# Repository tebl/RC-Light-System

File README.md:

# RC Light System
The *Arduino Starter Kit*, the official one with a bunch of parts and a book, was my first real introduction to working with electronics. Sure, I had put a new power plug on various things as a child of a different time that this one. What I hadn't done, was learn how to not blow things up when trying out new things. Arduino is pretty much perfect for that. Not in that you won't blow things up, it's more a case of blowing up really cheap parts and you rarely, if ever, actually set anything on fire. Working through it all, I wanted to create a project of my own - I would make a better light system for RCs.

Yeah! Turns out that doing exactly that, requires understanding a lot more than simply plugging an LED into a breadboard and turning it on or off - there's logic levels, reading a PWM signal and then figuring out how to design your own PCBs. So I eventually put my parts in the infamous *"someday"* pile. A decade later, I've learned a few things and it was time to take something off that pile and try again! 

As I had a lot of fun doing it, I wanted to build a multitude of slightly different things around the same core theme - RCs, lighting and cool effects. For that reason I found it easier to organize them into their own sub-projects, so follow the links to the ones you are specifically interested in.

- [1> Projects](#1-projects)
  - [1.1> RC Light System](#11-rc-light-system)
  - [1.2> RC Exhaust](#12-rc-exhaust)
  - [1.3> RC Dashboard](#13-rc-dashboard)

# 1> Projects
For the technical details as well as information regarding the projects included in this specific github repository, consult the table below and follow along for the things that may interest you.  As each project will realistically end up being done in several different ways, they will each come with their own set of documentation as well as BOM-listings - these are organized by putting all that into the documentation for each module below it. Organized separately, you are also recommended to check out the [schematics](https://github.com/tebl/RC-Light-System/tree/main/documentation/schematic) for detailed information about how the electrical side of things work.

| Module                            | Description                                      |
| --------------------------------- | ------------------------------------------------ | 
| [RC Light System](#11-rc-light-system)  | A functional light system for RCs. It's big, bulky and does mostly what I want it to do.
| [RC Exhaust](#12-rc-exhaust) | Controls an RGB LED mounted inside the exhaust pipe of an RC. On heavy throttle it starts glowing red, ease up on the trottle afterwards and you get flashing colours as it backfires.
| [RC Dashboard](#13-rc-dashboard) | Connected to the receiver, it shows a digital throttle gauge on a small OLED-screen.

## 1.1> RC Light System
This is the project I had originally intended to design, almost a decade earlier. A lighting system with some kind of recognizable intelligence to it. More specifically, something that wouldn't turn on the blinkers when turning the wheel. I could always just cut the wire, but I wanted it to work so that it felt more *scale* - turning on the blinker when cornering around a racetrack at subsonic speeds wasn't it. My second requirement was that it should be detachable by cable, mostly so that the electronics mounted on the chassis could be separated from those that are stuck to the body.

I can't physically work with small components, so as for any practical usage you will need a lot of space to install this - possibly a truck of some kind. Other than that, consider it *educational* material for anyone that wants to connect an Arduino to an RC-receiver.

| Module                            | Description                                      |
| --------------------------------- | ------------------------------------------------ | 
| [RC Light System](https://github.com/tebl/RC-Light-System/tree/main/RC%20Light%20System)  | Main module for mounting on chassis, uses Arduino Pro Micro.
| [RC Light System Output](https://github.com/tebl/RC-Light-System/tree/main/RC%20Light%20System%20Output)  | Output-module for mounting on a body. Four sets of two LEDs can be combined to have two levels of brightness.
| [RC Light System Output Mini](https://github.com/tebl/RC-Light-System/tree/main/RC%20Light%20System%20Output%20Mini)  | Output-module for mounting on a body. Slightly smaller than the other one, with almost none of the interesting features apart from turning LEDs on and off.

## 1.2> RC Exhaust
Working with the [RC Light System](#11-rc-light-system), I came across small metal exhaust pipes for 1:10 RCs on AliExpress. Arriving in the mail a couple of months later I knew I had to install them in something, given that they were designed to fit an LED inside it - I wanted something more exciting than a basic effect. I wanted it to glow red on heavy throttle, backfire when easing up on the throttle and so on!

| Module                            | Description                                      |
| --------------------------------- | ------------------------------------------------ | 
| [RC Exhaust Digispark](https://github.com/tebl/RC-Light-System/tree/main/RC%20Exhaust%20Digispark)  | Exhaust-module based around Digispark, with capability for RGB colour LED.

## 1.3> RC Dashboard
Tightly related to the [RC Exhaust](#12-rc-exhaust) in terms of implementation, mostly because I initially couldn't get it to work - so in the end I had to put a screen on one, all in order to figure out all the ways it had initially failed to work. That doesn't sound like a fun thing to build, but when doing it I had an idea - why not mount the screen inside the interior of an RC car? Cars generally have those, we call them *"dashboards"*.

An electric RC doesn't exactly have a lot of telemetry that's available to plug into, but at least I can put a throttle gauge on it. Nowadays you'd probably want an analog one, but I designed this one to mimic the digital future that was on display in a limited selection of 80s and 90s cars - check out [The definitive collection of cool 1980s digital dashboards in Euro cars
](https://drivemag.com/red-calipers/the-definitive-collection-of-cool-1980s-digital-dashboards-in-euro-cars/) to see some examples of what I'm talking about here.

| Module                            | Description                                      |
| --------------------------------- | ------------------------------------------------ | 
| [RC Dashboard Digispark](https://github.com/tebl/RC-Light-System/tree/main/RC%20Dashboard%20Digispark)  | Dashboard-module based around Digispark.

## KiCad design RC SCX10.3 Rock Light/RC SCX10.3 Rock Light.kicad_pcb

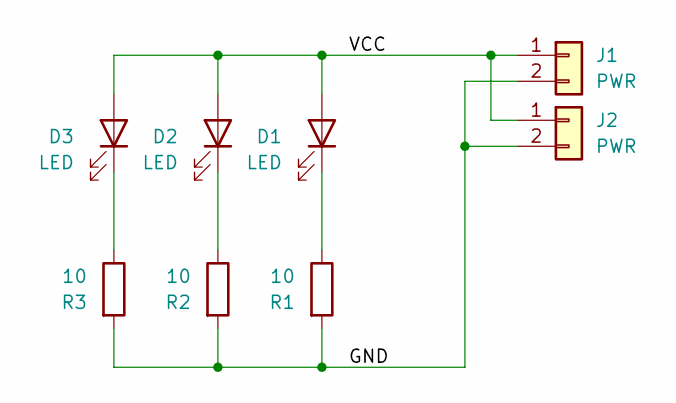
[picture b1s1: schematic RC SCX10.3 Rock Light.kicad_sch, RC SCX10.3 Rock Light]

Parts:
D1, D2, D3: LED; LED_1206_3216Metric_Pad1.42x1.75mm_HandSolder
J1, J2: PWR; edge_pins_1x02
R1, R2, R3: 10; R_1206_3216Metric_Pad1.30x1.75mm_HandSolder

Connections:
/GND: J1.2, J2.2, R1.2, R2.2, R3.2
/VCC: D1.2 (A), D2.2 (A), D3.2 (A), J1.1, J2.1
unnamed: D1.1 (K), R1.1
unnamed: D2.1 (K), R2.1
unnamed: D3.1 (K), R3.1

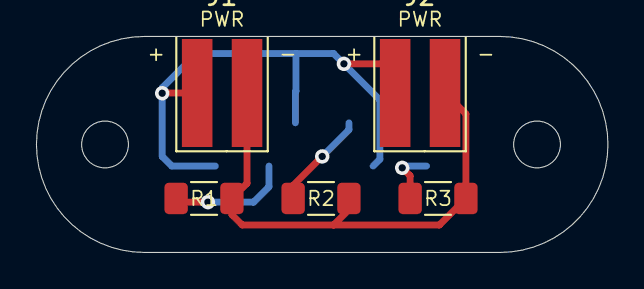
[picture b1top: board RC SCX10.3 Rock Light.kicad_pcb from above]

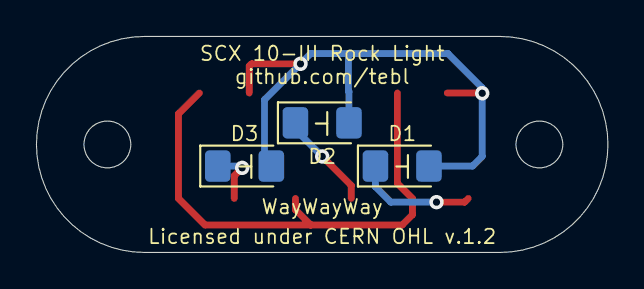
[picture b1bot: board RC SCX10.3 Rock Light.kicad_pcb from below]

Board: 2 copper layers, 31.8 x 12.0 mm, 8 parts (3 on the bottom side), 5 nets.

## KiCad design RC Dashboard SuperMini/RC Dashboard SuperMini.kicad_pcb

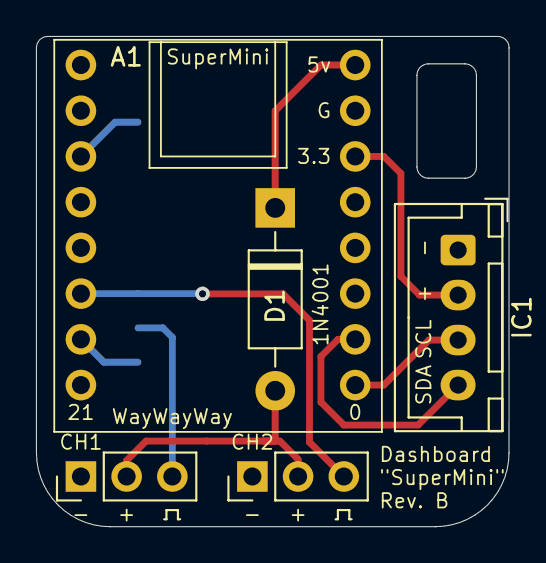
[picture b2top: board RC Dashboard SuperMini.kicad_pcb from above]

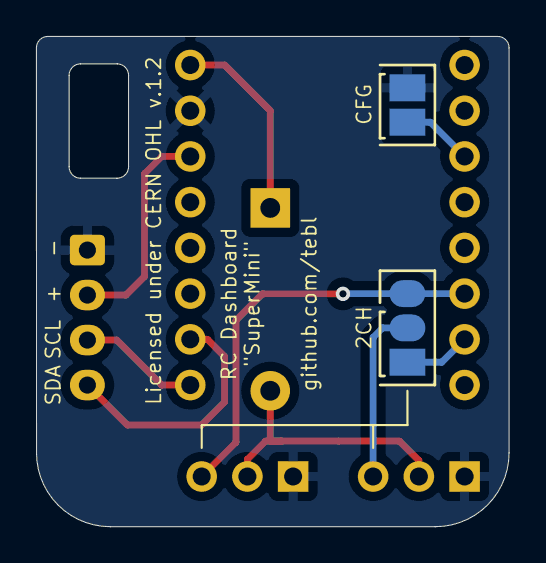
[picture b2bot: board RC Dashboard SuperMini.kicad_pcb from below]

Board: 2 copper layers, 26.3 x 27.2 mm, 7 parts (2 on the bottom side), 10 nets.

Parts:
A1: SuperMini; SuperMini_ESP32_C3
D1: 1N4001; D_DO-41_SOD81_P10.16mm_Horizontal
IC1: 0.91_I2C_OLED; JST_XH_B4B-XH-A_1x04_P2.50mm_Vertical
J5: CH1; PinHeader_1x03_P2.54mm_Vertical
J6: CH2; PinHeader_1x03_P2.54mm_Vertical
JP1: 2CH; select2
JP3: CFG; bridge

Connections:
+3V3: A1.14 (3V3), IC1.2 (VCC)
/6v: D1.2 (A), J5.2 (BEC), J6.2 (BEC)
/CFG_2: A1.3 (GPIO7), JP3.2 (B)
/SCL: A1.9 (GPIO0), IC1.3 (SCL)
/SDA: A1.10 (GPIO1), IC1.4 (SDA)
CH1: A1.7 (GPIO20), JP1.1 (A)
CH2: A1.6 (GPIO10), J6.3 (VCC), JP1.3 (B)
GND: A1.15 (GND), IC1.1 (GND), J5.1 (GND), J6.1 (GND), JP3.1 (A)
unnamed: J5.3 (VCC), JP1.2 (C)
VBUS: A1.16 (5v), D1.1 (K)

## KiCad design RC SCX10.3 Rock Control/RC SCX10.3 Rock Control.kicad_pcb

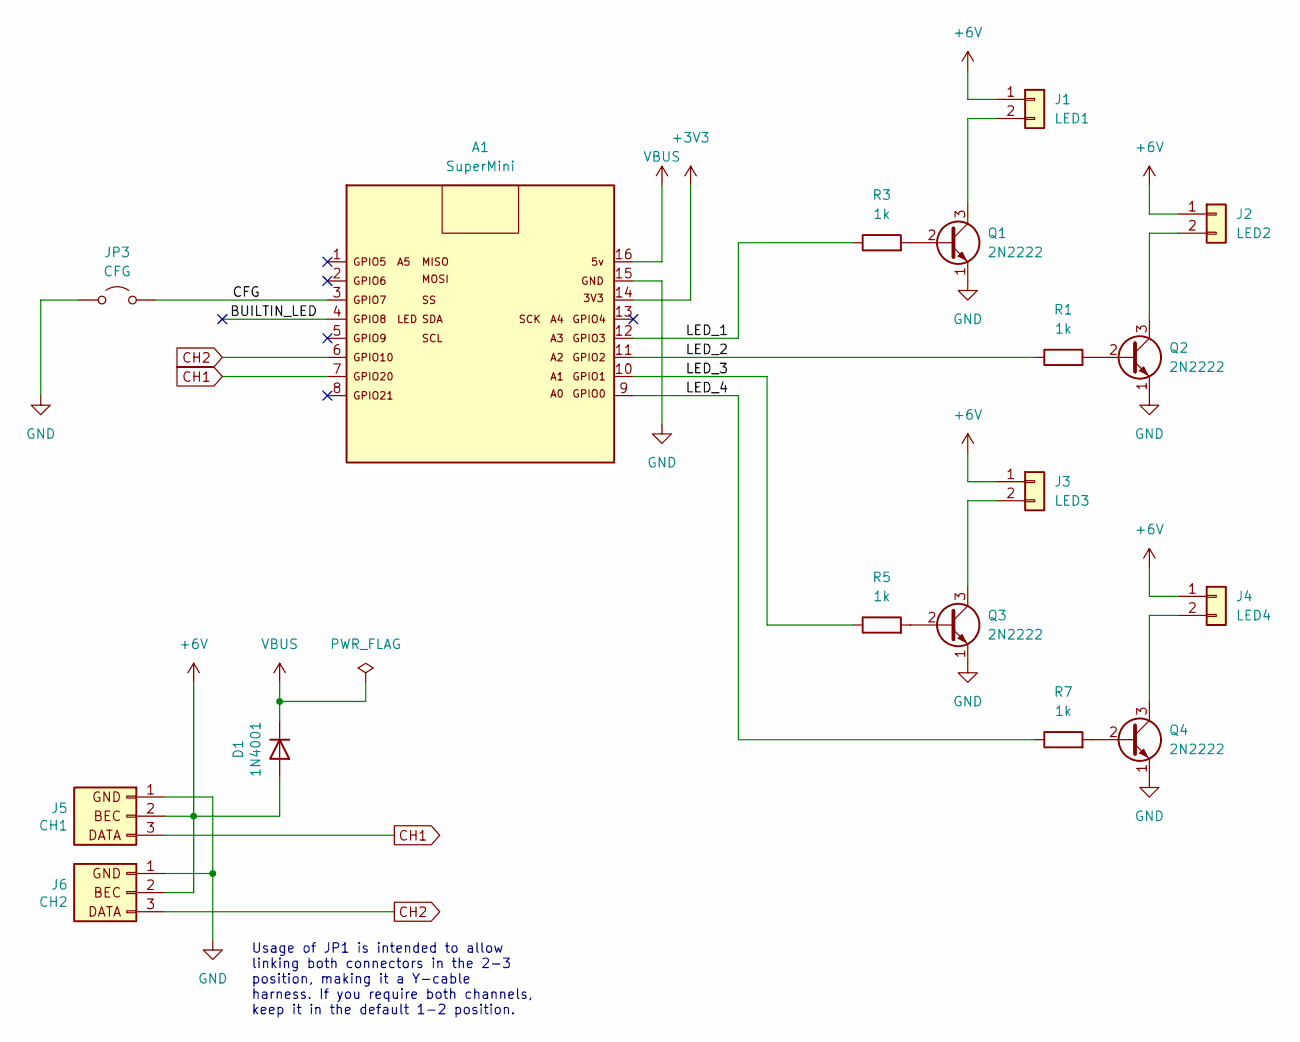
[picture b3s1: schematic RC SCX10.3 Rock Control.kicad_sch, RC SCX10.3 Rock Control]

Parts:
A1: SuperMini; SuperMini_ESP32_C3
D1: 1N4001; D_DO-41_SOD81_P10.16mm_Horizontal
J1: LED1; JST_XH_B2B-XH-A_1x02_P2.50mm_Vertical
J2: LED2; JST_XH_B2B-XH-A_1x02_P2.50mm_Vertical
J3: LED3; JST_XH_B2B-XH-A_1x02_P2.50mm_Vertical
J4: LED4; JST_XH_B2B-XH-A_1x02_P2.50mm_Vertical
J5: CH1; PinHeader_1x03_P2.54mm_Vertical
J6: CH2; PinHeader_1x03_P2.54mm_Vertical
JP3: CFG; bridge
Q1, Q2, Q3, Q4: 2N2222; TO-92_Inline_Wide
R1, R3, R5, R7: 1k; R_Axial_DIN0207_L6.3mm_D2.5mm_P7.62mm_Horizontal

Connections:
+3V3: A1.14 (3V3)
+6V: D1.2 (A), J1.1, J2.1, J3.1, J4.1, J5.2 (BEC), J6.2 (BEC)
/BUILTIN_LED: A1.4 (GPIO8)
/CFG: A1.3 (GPIO7), JP3.2 (B)
/LED_1: A1.12 (GPIO3), R3.1
/LED_2: A1.11 (GPIO2), R1.1
/LED_3: A1.10 (GPIO1), R5.1
/LED_4: A1.9 (GPIO0), R7.1
CH1: A1.7 (GPIO20), J5.3 (VCC)
CH2: A1.6 (GPIO10), J6.3 (VCC)
GND: A1.15 (GND), J5.1 (GND), J6.1 (GND), JP3.1 (A), Q1.1 (E), Q2.1 (E), Q3.1 (E), Q4.1 (E)
unnamed: J1.2, Q1.3 (C)
unnamed: J2.2, Q2.3 (C)
unnamed: J3.2, Q3.3 (C)
unnamed: J4.2, Q4.3 (C)
unnamed: Q1.2 (B), R3.2
unnamed: Q2.2 (B), R1.2
unnamed: Q3.2 (B), R5.2
unnamed: Q4.2 (B), R7.2
VBUS: A1.16 (5v), D1.1 (K)

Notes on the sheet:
Usage of JP1 is intended to allow linking both connectors in the 2-3 position, making it a Y-cable harness. If you require both channels, keep it in the default 1-2 position.

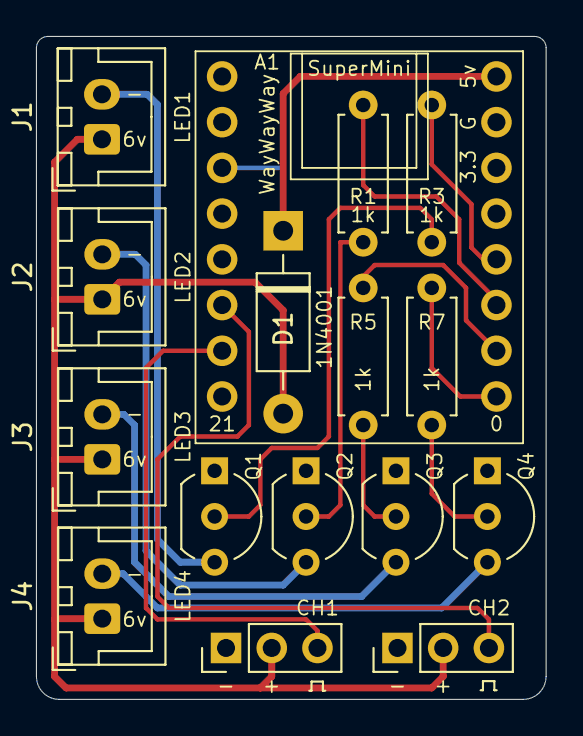
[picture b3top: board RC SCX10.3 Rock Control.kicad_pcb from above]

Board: 2 copper layers, 28.3 x 36.8 mm, 17 parts (1 on the bottom side), 18 nets.

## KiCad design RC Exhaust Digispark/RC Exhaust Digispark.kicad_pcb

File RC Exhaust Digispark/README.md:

# RC Exhaust (Digispark)
Working with the RC Light System, I came across a small metal exhaust pipe for 1:10 RCs on AliExpress. Arriving in the mail a couple of months later, I knew I had to install them in something. Careful measuring revealed that they were designed to fit an LED inside it, and later versions that I picked up even came with one included. I did however want something that was a little more dynamic than a static LED could provide and while I could have gone with the 555, I went the full route of the Attiny85. Granted, I did have some Digispark modules that I'd never found a use for. Until now.

The plan was to have the exhaust pipe glow red on heavy throttle, then backfire when easing up on the throttle. It'll throw in some regular sparks here and there to make it come alive a bit more than that, but the code is included here if you want something else.

- [1> Building the device](#1-building-the-device)
- [2> Schematic](#2-schematic)
- [3> BOM](#3-bom)

# 1> Building the device
Building the device should be a straight-forward affair, you just solder the meager selection of components into place. Pay attention to keep the alignment of the parts somewhat straight, then you should be good. This documentation was written with a board that looks like the following in mind, but note that the github-repository may contain changes that have yet to be tested (therefore, it is recommend that PCBs are ordered using PCBWay links listed in the BOM).

The Attiny85 is a 5v chip, and we're connecting it to a 6v source due to it living inside an RC. Normally that would toast it as we're working outside the acceptable ranges, but we're using a diode with a voltage drop that's up to 0.7v - bringing us withing the tolerances of the chip. As for installation, just match the silver stripe on the component to the stripe part on the board and you're good to go.

Resistors should be added, but you can *probably* skip R4 and R5 - those form a voltage divider in case the receiver is sending out a signal that's above 3.3v. I've not encountered any of those, but then again - I don't have RC equipment older than a decade or so. Link the corresponding *NO_VOL_DIV* pads on the back of it if you've skipped them.

The three at the bottom are for the LEDs, here you may need to match the datasheet for your specific LED, per colour, in order to arrive at a suitable resistor value. Consult a [LED Series Resistor Calculator](https://www.digikey.com/en/resources/conversion-calculators/conversion-calculator-led-series-resistor) if you need to (set supply voltage to 5.3v, fill in 10mA current for blue/green and 15mA for red).

The Digispark itself is then soldered on top, with straight pin headers between the two. It doesn't matter if you used the Digispark shaped like a "USB-key", or if it has a Micro-USB socket on it - they fit just the same. Personally I prefer the former as it is easier to wipe off compared to pulling debris out of a socket.

The LED must be attached to the board using a removable lead, which is why I'm using JST XH plugs on mine. When wiring for an RGB LED it must be a common anode variety, but you can use a normal LED as well - just wire it up to the board as *RED*. If you don't care about being able to reprogram the board later, you can just solder the wires directly. When soldering onto the LED legs, I recommend using heat shrink tubing to avoid any accidents. An easier alternative is to use a pre-wired red LED and just connect up those two leads, but won't look as fancy.

The left hand side is where you connect up the wire coming from the ESC, there are two here - mainly so that you could use it as a Y-lead without requiring any additional cables. Solder wires, or install pin headers depending on what you prefer.

# 2> Schematic
The supplied KiCad files should be sufficient as both a schematic and as a  starting point for ordering PCBs (basically you could just zip the contents of the export folder and upload that on a fabrication site), the schematic is also available in [PDF-format](https://github.com/tebl/RC-Light-System/tree/main/documentation/schematic) and this is what you'll need to print and work your way through when things fail to work as expected.

# 3> BOM
Most parts should be easy to get a hold of from your favourite local electronic component shop, but given that I don't have access to such shops where I live so everything was based on whatever I could get cheapest from eBay/AliExpress (free shipping, but plan on waiting 3-4 weeks for delivery). As I expect that most will build this adapter solely for MIDI-output, the values required for the MIDI input have been listed in parenthesis.

| Reference      | Item                                                  | Count | Order  |
| ---------------| ----------------------------------------------------- | ----- | ------ |
| Faceplate PCB  | Fabricate using Gerber files                          |     1 | PCBWay
| A1             | Digispark-module (with pin-headers)                   |     1 |
| D1 *           | 4-pin JST-XH socket                                   |     1 |
|                | 5mm LED, common-anode variety to 4-pin JST-XH plug    |     1 |
| D2             | 1N4001 diode (DO-41)                                  |     1 |
| J5,J6          | Straight pin-headers, alternatively wire a Y-splitter |     1 |
| R1             | 200 ohm resistor                                      |     1 |
| R2,R3          | 270 ohm resistor                                      |     2 |
| R4             | 10k ohm resistor                                      |    (1)|
| R5             | 20k ohm resistor                                      |    (1)|

*) You can come up with something else here, but JST-XH is what I recommend. They're keyed and locking so they won't come off very easily. For the LED, I recommend buying pre-wired 4-pin JST-XH leads with plugs already on it - you'll need to solder it to the individual LED legs though (use heat shrink tubing).

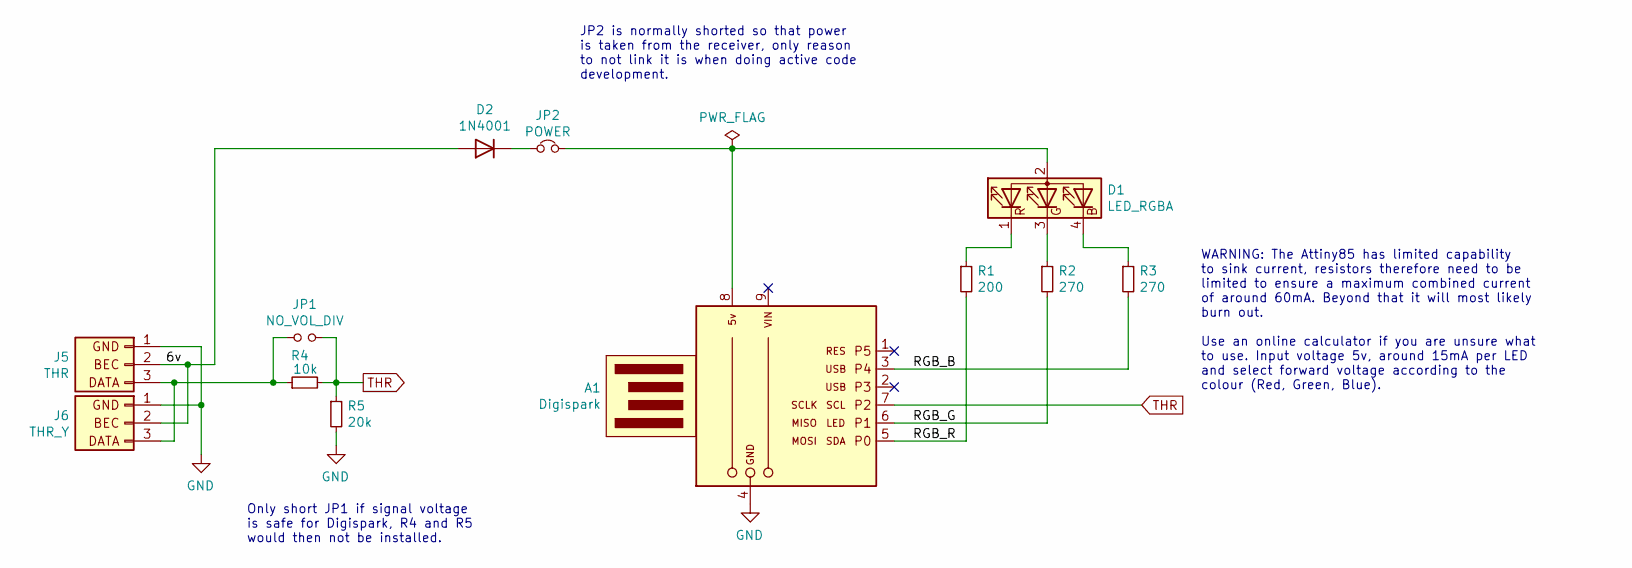
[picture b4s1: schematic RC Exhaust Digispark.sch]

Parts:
A1: Digispark
D1: LED_RGBA; JST_XH_B4B-XH-A_1x04_P2.50mm_Vertical
D2: 1N4001; D_DO-41_SOD81_P10.16mm_Horizontal
J5: THR; PinHeader_1x03_P2.54mm_Vertical
J6: THR_Y; PinHeader_1x03_P2.54mm_Vertical
JP1: NO_VOL_DIV; bridge_open
JP2: POWER; bridge
R1: 200; R_Axial_DIN0207_L6.3mm_D2.5mm_P7.62mm_Horizontal
R2, R3: 270; R_Axial_DIN0207_L6.3mm_D2.5mm_P7.62mm_Horizontal
R4: 10k; R_Axial_DIN0207_L6.3mm_D2.5mm_P7.62mm_Horizontal
R5: 20k; R_Axial_DIN0207_L6.3mm_D2.5mm_P7.62mm_Horizontal

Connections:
/6v: D2.2 (A), J5.2 (BEC), J6.2 (BEC)
/RGB_B: A1.3 (P4), R3.2
/RGB_G: A1.6 (P1), R2.2
/RGB_R: A1.5 (P0), R1.2
GND: A1.4 (GND), J5.1 (GND), J6.1 (GND), R5.2
unnamed: A1.8 (5v), D1.2 (A), JP2.2
unnamed: D1.1 (RK), R1.1
unnamed: D1.3 (GK), R2.1
unnamed: D1.4 (BK), R3.1
unnamed: D2.1 (K), JP2.1
unnamed: J5.3 (VCC), J6.3 (VCC), JP1.1, R4.1
THR: A1.7 (P2), JP1.2, R4.2, R5.1

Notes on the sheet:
Only short JP1 if signal voltage is safe for Digispark, R4 and R5 would then not be installed.
JP2 is normally shorted so that power is taken from the receiver, only reason to not link it is when doing active code development.
WARNING: The Attiny85 has limited capability to sink current, resistors therefore need to be limited to ensure a maximum combined current of around 60mA. Beyond that it will most likely burn out. Use an online calculator if you are unsure what to use. Input voltage 5v, around 15mA per LED and selec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

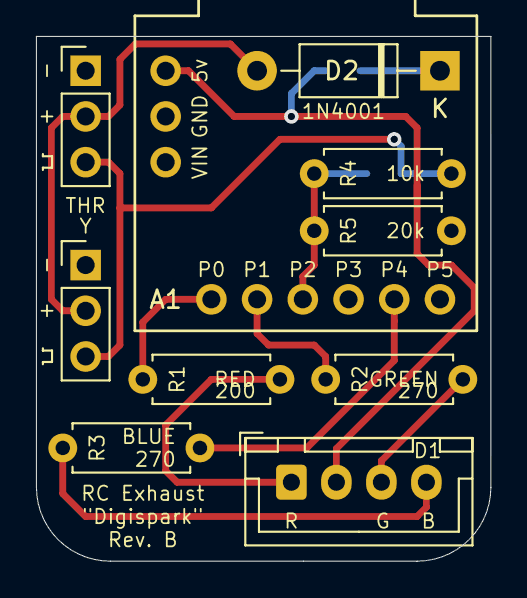
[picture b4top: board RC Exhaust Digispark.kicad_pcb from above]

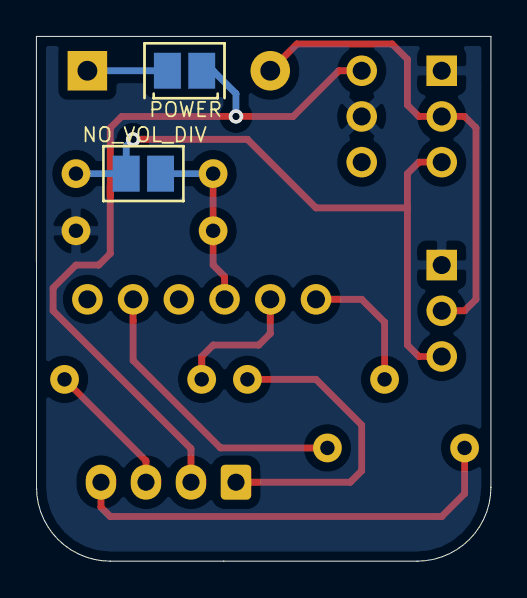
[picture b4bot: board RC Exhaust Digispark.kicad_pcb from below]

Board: 2 copper layers, 25.2 x 29.2 mm, 12 parts (2 on the bottom side), 12 nets.

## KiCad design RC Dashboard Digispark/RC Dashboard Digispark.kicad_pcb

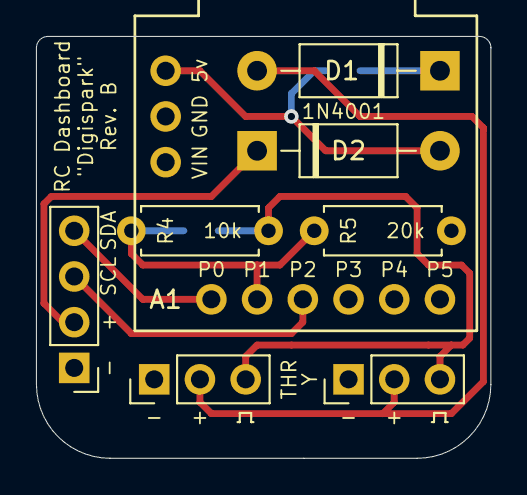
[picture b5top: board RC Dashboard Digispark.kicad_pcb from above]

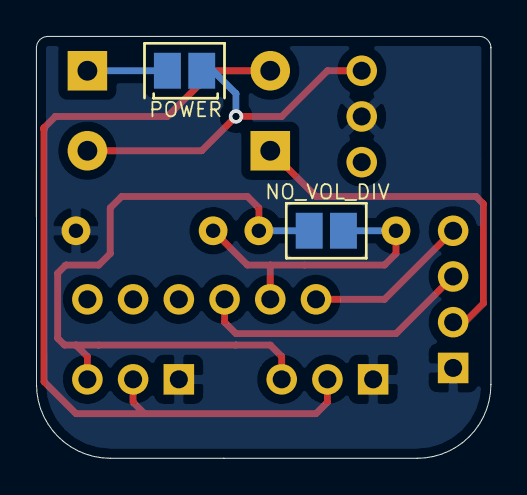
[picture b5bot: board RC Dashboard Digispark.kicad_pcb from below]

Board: 2 copper layers, 25.2 x 23.4 mm, 10 parts (2 on the bottom side), 9 nets.

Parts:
A1: Digispark
D1, D2: 1N4001; D_DO-41_SOD81_P10.16mm_Horizontal
IC1: 0.91_I2C_OLED; PinHeader_1x04_P2.54mm_Vertical
J5: THR; PinHeader_1x03_P2.54mm_Vertical
J6: THR_Y; PinHeader_1x03_P2.54mm_Vertical
JP1: NO_VOL_DIV; bridge_open
JP2: POWER; bridge
R4: 10k; R_Axial_DIN0207_L6.3mm_D2.5mm_P7.62mm_Horizontal
R5: 20k; R_Axial_DIN0207_L6.3mm_D2.5mm_P7.62mm_Horizontal

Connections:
/6v: D1.2, J5.2, J6.2
GND: A1.4, IC1.1, J5.1, J6.1, R5.2
unnamed: A1.5, IC1.4
unnamed: A1.7, IC1.3
unnamed: A1.8, D2.2, JP2.2
unnamed: D1.1, JP2.1
unnamed: D2.1, IC1.2
unnamed: J5.3, J6.3, JP1.1, R4.1
THR: A1.6, JP1.2, R4.2, R5.1

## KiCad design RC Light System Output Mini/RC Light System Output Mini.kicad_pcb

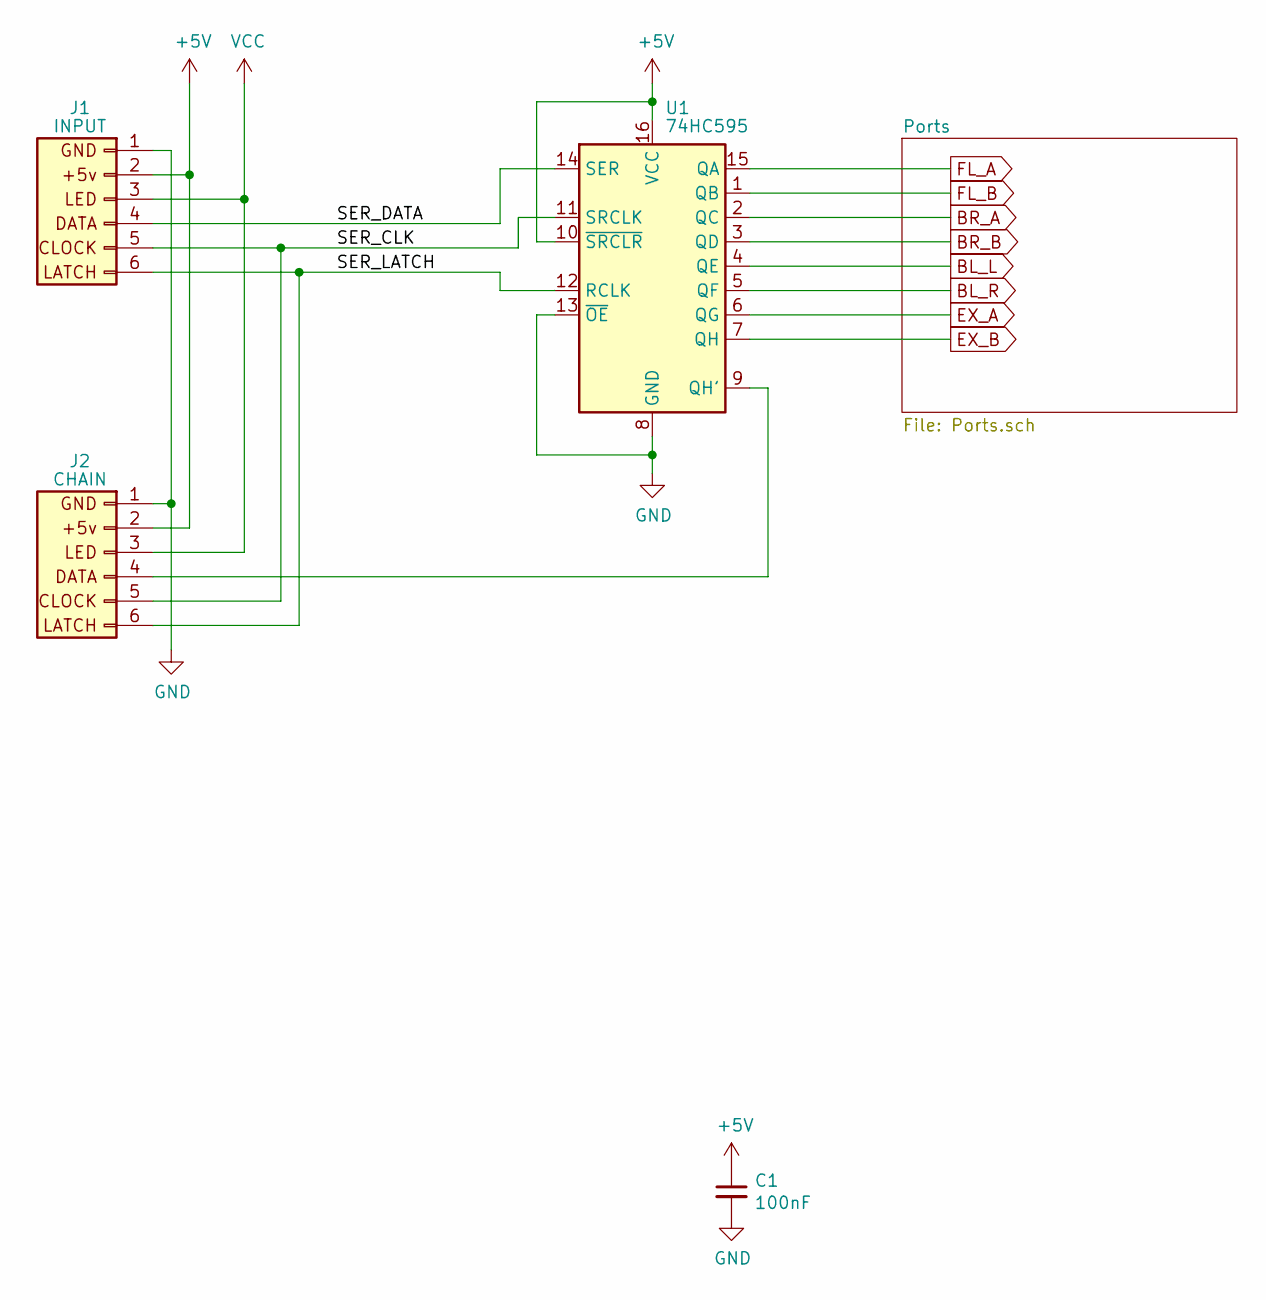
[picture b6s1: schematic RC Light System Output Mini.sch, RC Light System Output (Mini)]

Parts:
C1: 100nF; C_Disc_D4.7mm_W2.5mm_P5.00mm
J1: INPUT; JST_XH_B6B-XH-A_1x06_P2.50mm_Vertical
J2: CHAIN; JST_XH_B6B-XH-A_1x06_P2.50mm_Vertical
U1: 74HC595; DIP-16_W7.62mm_Socket_LongPads

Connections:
+5V: C1.1, J1.2 (+5V), J2.2 (+5V), U1.10 (~SRCLR), U1.16 (VCC)
/SER_CLK: J1.5 (CLOCK), J2.5 (CLOCK), U1.11 (SRCLK)
/SER_DATA: J1.4 (DATA), U1.14 (SER)
/SER_LATCH: J1.6 (LATCH), J2.6 (LATCH), U1.12 (RCLK)
BL_L: U1.4 (QE); also elsewhere on the board
BL_R: U1.5 (QF); also elsewhere on the board
BR_A: U1.2 (QC); also elsewhere on the board
BR_B: U1.3 (QD); also elsewhere on the board
EX_A: U1.6 (QG); also elsewhere on the board
EX_B: U1.7 (QH); also elsewhere on the board
FL_A: U1.15 (QA); also elsewhere on the board
FL_B: U1.1 (QB); also elsewhere on the board
GND: C1.2, J1.1 (GND), J2.1 (GND), U1.8 (GND), U1.13 (~OE); also elsewhere on the board
unnamed: J2.4 (DATA), U1.9 (QH')
VCC: J1.3 (LED), J2.3 (LED)

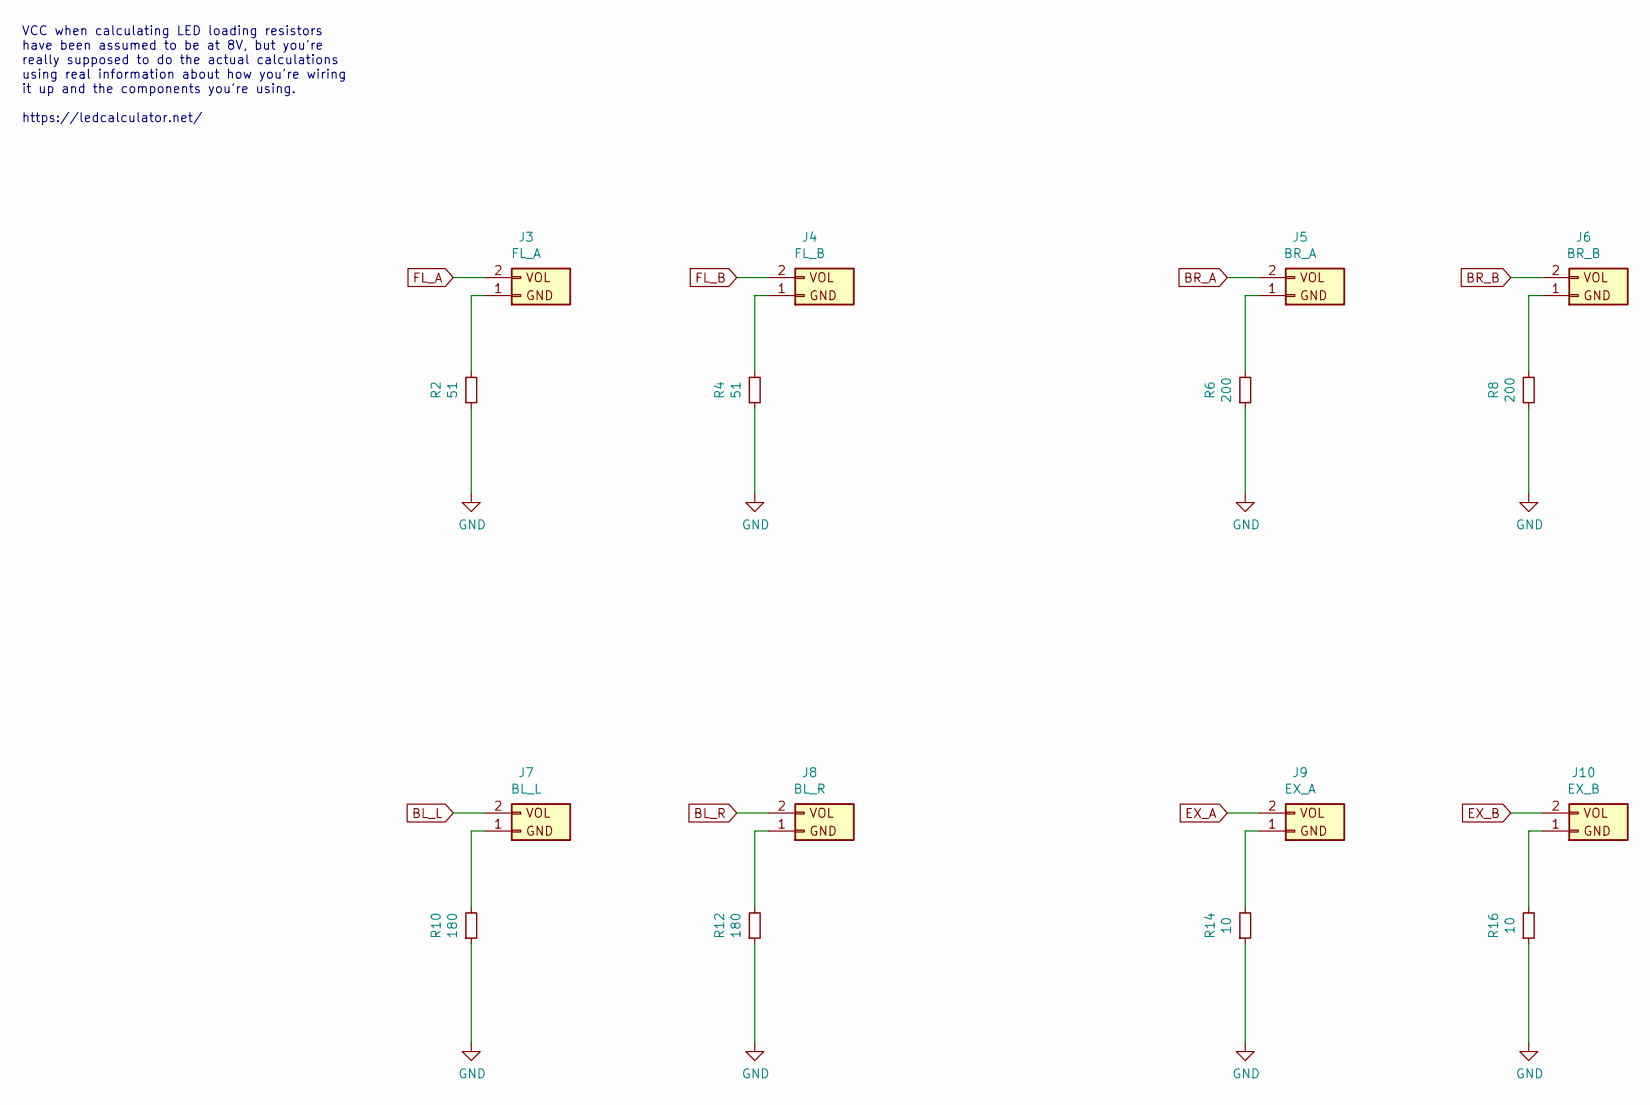
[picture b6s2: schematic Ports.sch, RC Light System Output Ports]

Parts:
J3: FL_A; JST_XH_B2B-XH-A_1x02_P2.50mm_Vertical
J4: FL_B; JST_XH_B2B-XH-A_1x02_P2.50mm_Vertical
J5: BR_A; JST_XH_B2B-XH-A_1x02_P2.50mm_Vertical
J6: BR_B; JST_XH_B2B-XH-A_1x02_P2.50mm_Vertical
J7: BL_L; JST_XH_B2B-XH-A_1x02_P2.50mm_Vertical
J8: BL_R; JST_XH_B2B-XH-A_1x02_P2.50mm_Vertical
J9: EX_A; JST_XH_B2B-XH-A_1x02_P2.50mm_Vertical
J10: EX_B; JST_XH_B2B-XH-A_1x02_P2.50mm_Vertical
R2, R4: 51; R_Axial_DIN0207_L6.3mm_D2.5mm_P7.62mm_Horizontal
R6, R8: 200; R_Axial_DIN0207_L6.3mm_D2.5mm_P7.62mm_Horizontal
R10, R12: 180; R_Axial_DIN0207_L6.3mm_D2.5mm_P7.62mm_Horizontal
R14, R16: 10; R_Axial_DIN0207_L6.3mm_D2.5mm_P7.62mm_Horizontal

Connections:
BL_L: J7.2 (+5V); also elsewhere on the board
BL_R: J8.2 (+5V); also elsewhere on the board
BR_A: J5.2 (+5V); also elsewhere on the board
BR_B: J6.2 (+5V); also elsewhere on the board
EX_A: J9.2 (+5V); also elsewhere on the board
EX_B: J10.2 (+5V); also elsewhere on the board
FL_A: J3.2 (+5V); also elsewhere on the board
FL_B: J4.2 (+5V); also elsewhere on the board
GND: R2.1, R4.1, R6.1, R8.1, R10.1, R12.1, R14.1, R16.1; also elsewhere on the board
unnamed: J3.1 (GND), R2.2
unnamed: J4.1 (GND), R4.2
unnamed: J5.1 (GND), R6.2
unnamed: J6.1 (GND), R8.2
unnamed: J7.1 (GND), R10.2
unnamed: J8.1 (GND), R12.2
unnamed: J9.1 (GND), R14.2
unnamed: J10.1 (GND), R16.2

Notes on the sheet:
VCC when calculating LED loading resistors have been assumed to be at 8V, but you're really supposed to do the actual calculations using real information about how you're wiring it up and the components you're using. https://ledcalculator.net/

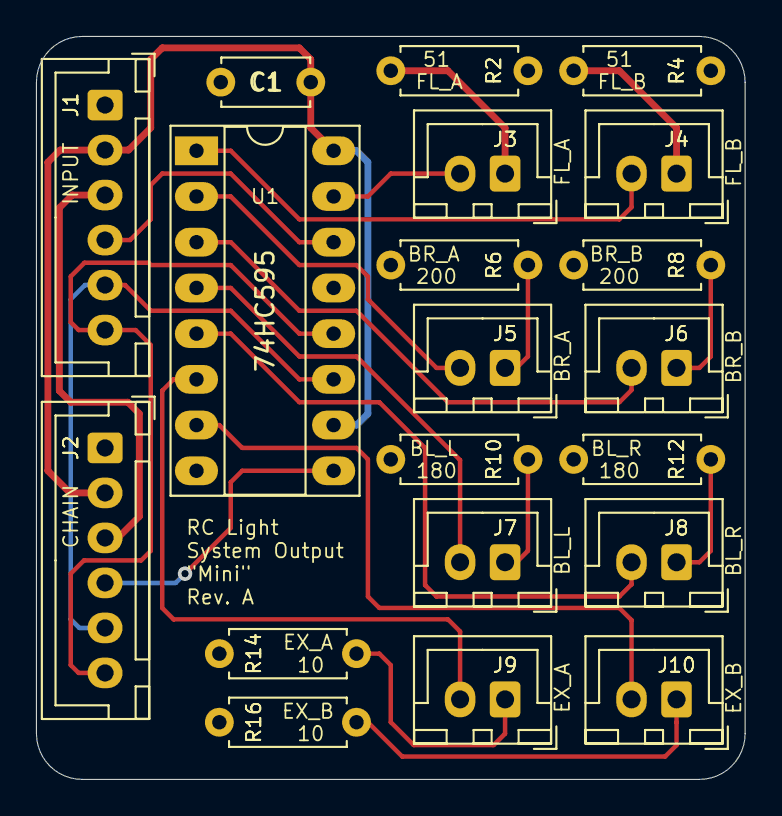
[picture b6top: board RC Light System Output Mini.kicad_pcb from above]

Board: 2 copper layers, 39.4 x 41.3 mm, 20 parts (0 on the bottom side), 23 nets.

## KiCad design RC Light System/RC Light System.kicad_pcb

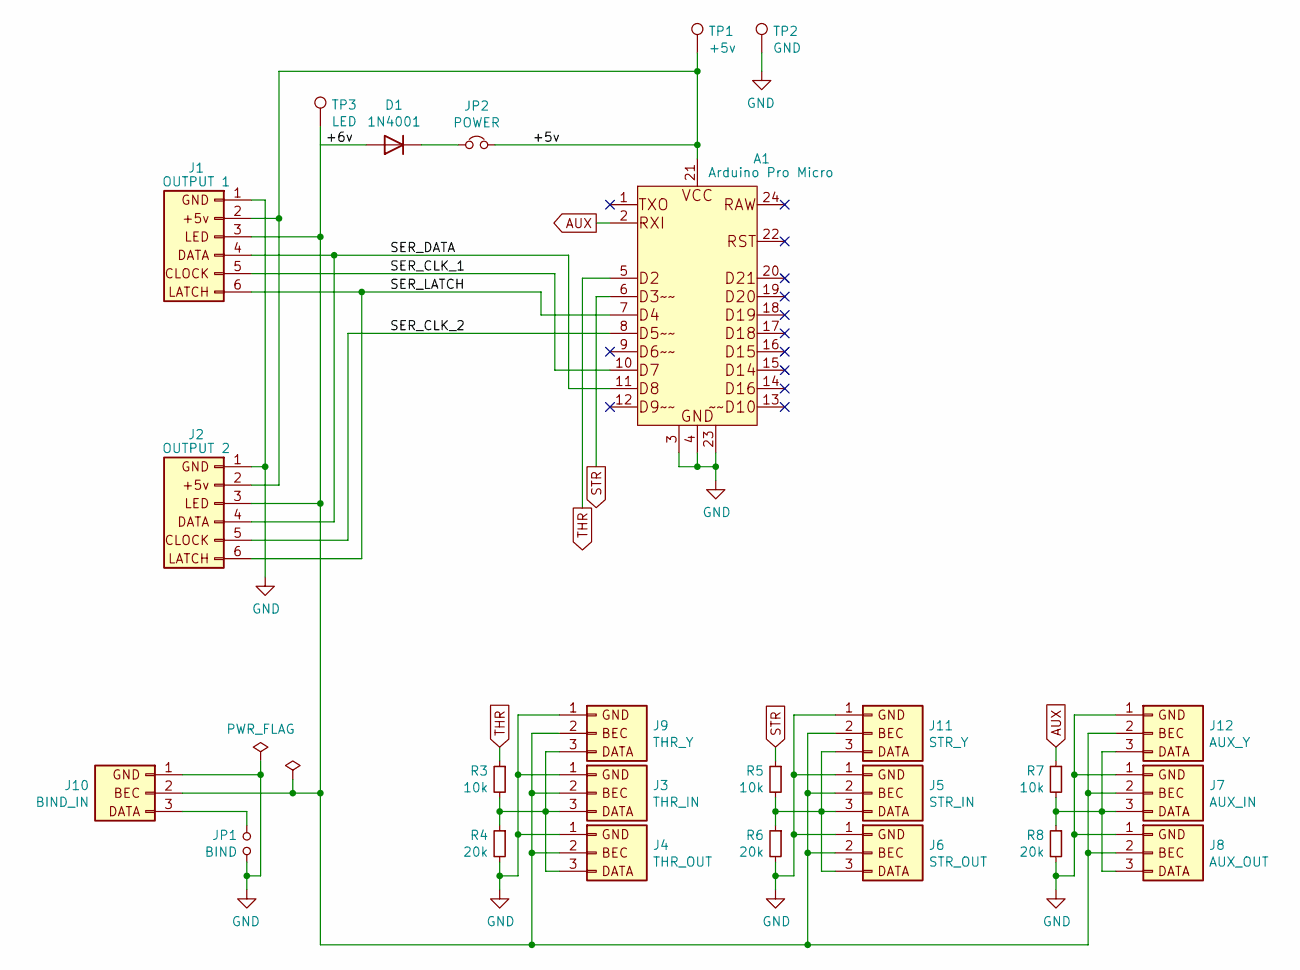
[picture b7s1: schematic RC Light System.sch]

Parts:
A1: Arduino Pro Micro; Arduino_Pro_Micro
D1: 1N4001; D_DO-41_SOD81_P10.16mm_Horizontal
J1: OUTPUT 1; JST_XH_B6B-XH-A_1x06_P2.50mm_Vertical
J2: OUTPUT 2; JST_XH_B6B-XH-A_1x06_P2.50mm_Vertical
J3: THR_IN; PinSocket_1x03_P2.54mm_Vertical
J4: THR_OUT; PinHeader_1x03_P2.54mm_Vertical
J5: STR_IN; PinSocket_1x03_P2.54mm_Vertical
J6: STR_OUT; PinHeader_1x03_P2.54mm_Vertical
J7: AUX_IN; PinSocket_1x03_P2.54mm_Vertical
J8: AUX_OUT; PinHeader_1x03_P2.54mm_Vertical
J9: THR_Y; PinHeader_1x03_P2.54mm_Vertical
J10: BIND_IN; PinSocket_1x03_P2.54mm_Vertical
J11: STR_Y; PinHeader_1x03_P2.54mm_Vertical
J12: AUX_Y; PinHeader_1x03_P2.54mm_Vertical
JP1: BIND; PinHeader_1x02_P2.54mm_Vertical
JP2: POWER; bridge
R3, R5, R7: 10k; R_Axial_DIN0207_L6.3mm_D2.5mm_P7.62mm_Horizontal
R4, R6, R8: 20k; R_Axial_DIN0207_L6.3mm_D2.5mm_P7.62mm_Horizontal
TP1: +5v; Testpoint
TP2: GND; Testpoint
TP3: LED; Testpoint

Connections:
/+5v: A1.21 (VCC), J1.2 (+5V), J2.2 (+5V), JP2.2, TP1.1
/+6v: D1.2 (A), J1.3 (LED), J2.3 (LED), J3.2 (BEC), J4.2 (BEC), J5.2 (BEC), J6.2 (BEC), J7.2 (BEC), J8.2 (BEC), J9.2 (BEC), J10.2 (BEC), J11.2 (BEC), J12.2 (BEC), TP3.1
/SER_CLK_1: A1.10 (D7), J1.5 (CLOCK)
/SER_CLK_2: A1.8 (D5), J2.5 (CLOCK)
/SER_DATA: A1.11 (D8), J1.4 (DATA), J2.4 (DATA)
/SER_LATCH: A1.7 (D4), J1.6 (LATCH), J2.6 (LATCH)
AUX: A1.2 (RXI), R7.1
GND: A1.3 (GND), A1.4 (GND), A1.23 (GND), J1.1 (GND), J2.1 (GND), J3.1 (GND), J4.1 (GND), J5.1 (GND), J6.1 (GND), J7.1 (GND), J8.1 (GND), J9.1 (GND), J10.1 (GND), J11.1 (GND), J12.1 (GND), JP1.1, R4.2, R6.2, R8.2, TP2.1
unnamed: D1.1 (K), JP2.1
unnamed: J3.3 (VCC), J4.3 (VCC), J9.3 (VCC), R3.2, R4.1
unnamed: J10.3 (VCC), JP1.2
unnamed: J5.3 (VCC), J6.3 (VCC), J11.3 (VCC), R5.2, R6.1
unnamed: J7.3 (VCC), J8.3 (VCC), J12.3 (VCC), R7.2, R8.1
STR: A1.6 (D3), R5.1
THR: A1.5 (D2), R3.1

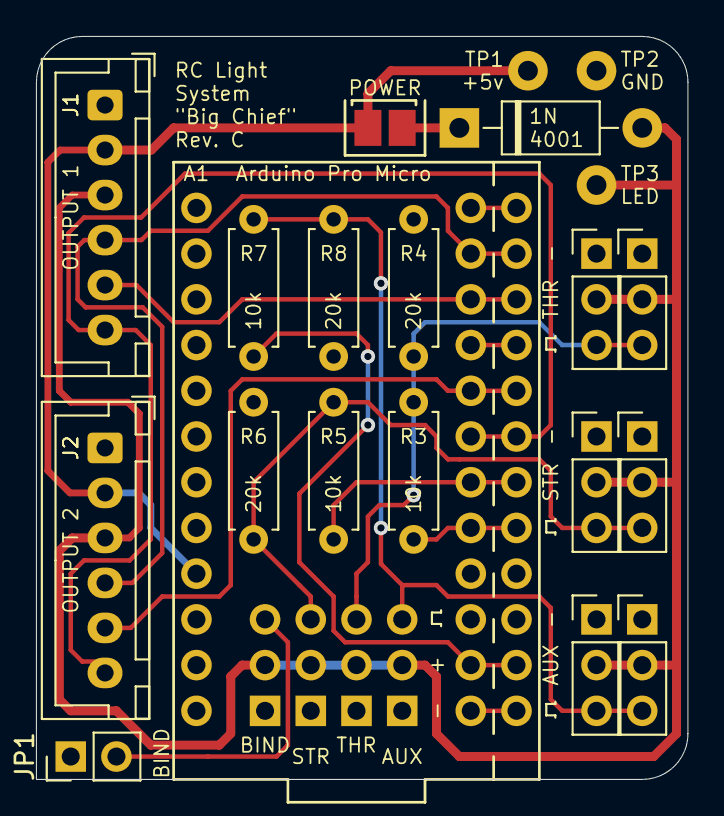
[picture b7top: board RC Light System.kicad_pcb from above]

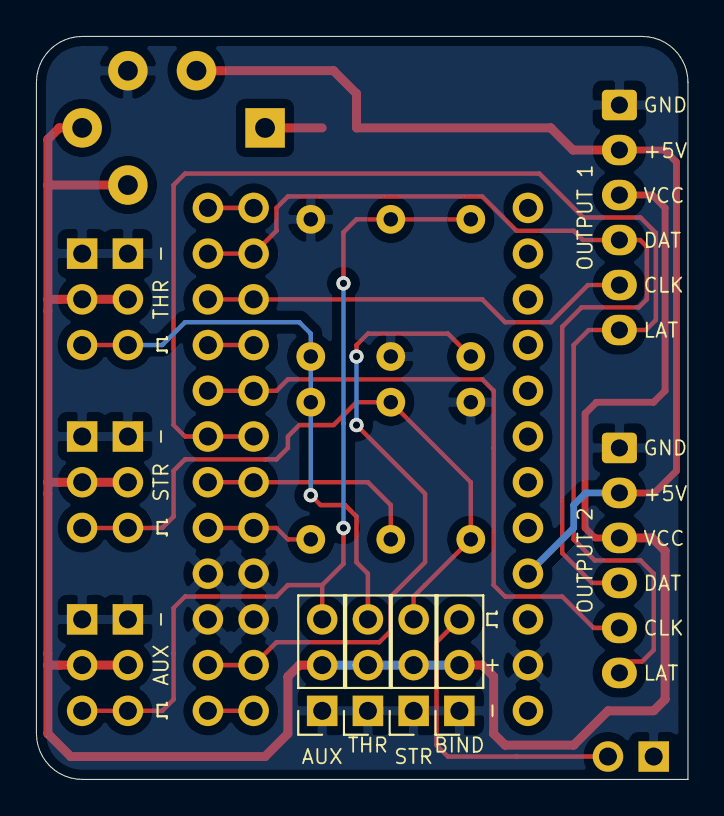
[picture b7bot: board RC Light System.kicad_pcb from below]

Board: 2 copper layers, 36.2 x 41.3 mm, 25 parts (4 on the bottom side), 15 nets.

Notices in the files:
RC Dashboard SuperMini/RC Dashboard SuperMini.kicad_pcb:
Licensed under CERN OHL v.1.2
